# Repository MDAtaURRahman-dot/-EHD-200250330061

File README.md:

# -EHD-200250330061
 EHD-200250330061

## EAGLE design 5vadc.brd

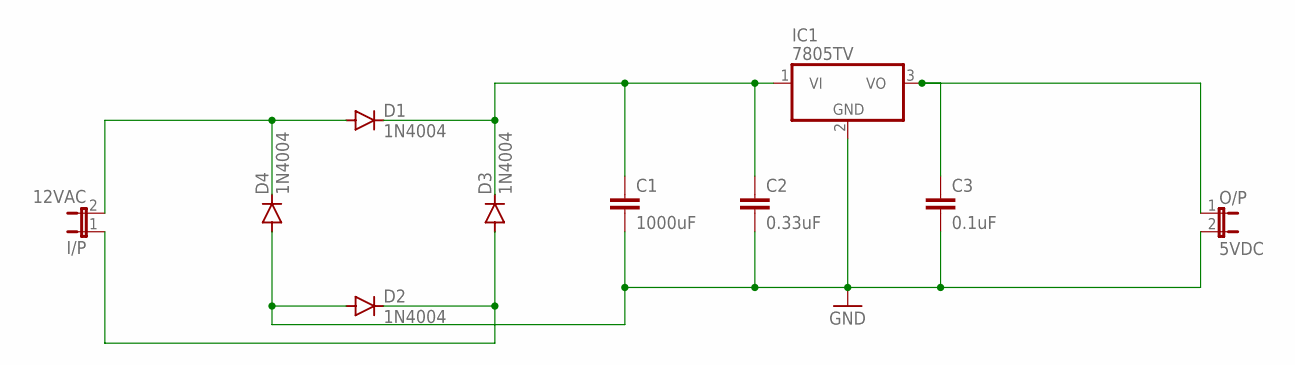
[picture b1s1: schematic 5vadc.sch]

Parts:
C1: 1000uF; C2.5-3
C2: 0.33uF; C2.5-3
C3: 0.1uF; C2.5-3
D1, D2, D3, D4: 1N4004; DO41-10
I/P: 12VAC; JP1
IC1: 7805TV; TO220V
O/P: 5VDC; JP1

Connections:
GND: C1.2, C2.2, C3.2, D2.A, D4.A, IC1.2 (GND), O/P.2
unnamed: C3.1, IC1.3 (VO), O/P.1
unnamed: D1.A, D4.C, I/P.2
unnamed: C1.1, C2.1, D1.C, D3.C, IC1.1 (VI)
unnamed: D2.C, D3.A, I/P.1

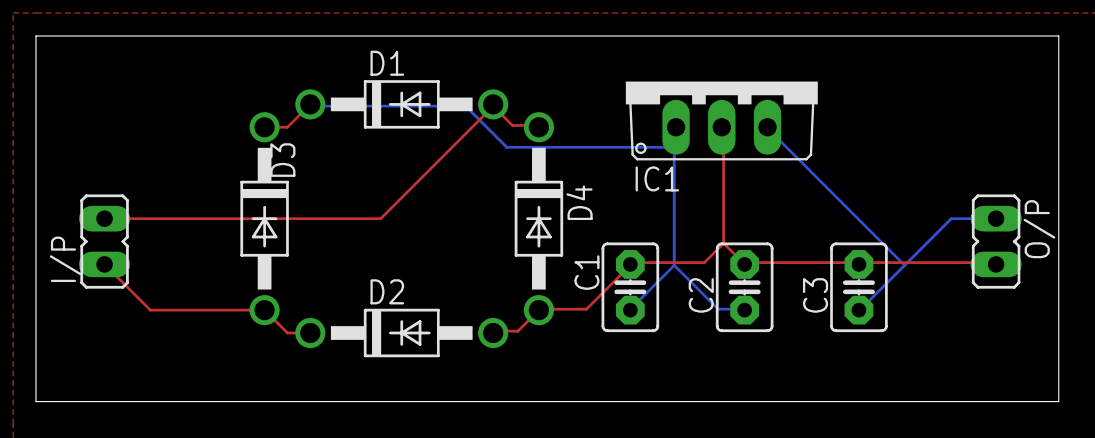
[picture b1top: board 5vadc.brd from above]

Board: 2 copper layers, 56.8 x 20.3 mm, 10 parts (0 on the bottom side), 5 nets.
